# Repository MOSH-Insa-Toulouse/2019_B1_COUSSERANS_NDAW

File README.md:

# MOSH Project : LoRa Arduino Board (Martin Cousserans/Aly Ndaw)

In this project we decided to focus on the PCB design and for the programming part we just implemented the RX/TX communication in LoRa. 
For the PCB we did a board that can act like a shield or a standalone connected gas sensor in LoRa by using selectors. 

## Getting Started

In our repertory you can find the files related to the PCB in ./LoRa_Arduino_Board. In it you have the two main files :
- the schematic file : LoRa_Arduino_Board.sch 
- the pcb file : LoRa_Arduino_Board.kicad_pcb
We let all libraries in the folder so it is easy to take the project and change it. 

### kiCAD Board

The board is a 2 layers board with a ground plane on each face of the board. There are components only on the top but we have tracks on both side. 
We have in total 37 components on the board. 
We can divided the board in four parts : 
- The gas sensor and its amplification chain 
- The RN2483 module 
- The Arduino Shield connectors 
- The standalone MCU (ATMEGA 328PU)

#### The gas sensor : 
Our solution is based on connectors and jumpers to select the behavior of the board. 
JRST-2 and JRST-4 are jumpers that allow to choose a specific configuration of the gas sensor GasLeft or GasRight. JRST-3 is the select for Gas sensor 1 or Gas sensor 2. 
JRST-5 allow us to select VIN to supply the heater resistor or an external DC source. 
JRST-6 is the jumper that select the output after the amplification we can connect it to the standalone MCU or the Arduino shield. 

#### The RN2483 module : 
We use 5 pins on the RN2483 (RST, RX, TX, 3V3, GND) module and we designed 5 jumpers (JRST-1, JRX1, JTX1, JTX2, JTX3) to switch them between the arduino shield and the standalone MCU. 
We also have a voltage divider bridge to have 3v3 from the 5V of the standalone MCU to supply the RN2483. 

#### The standalone MCU : 
For the ATMEGA MCU we have designed a 5 pins connector to program the chip with the Sparkfun Interface. And also we add another jumper to choose the main supply of the board. 
You can find images of the schematic and pcb in the LoRa_Arduino_Board folder if you want to have a preview. 

### LoRa Arduino Code

For the code we decided to follow the green track to be more focused on the PCB. 
We manage to do a downlink and uplink code with the LoRa platform of https://thethingsnetwork.org

Example : loop of the downlink code 
```
void loop()
{
    led_on();

    Serial.print("TXing");
    myLora.txCnf("!"); //one byte, blocking function

    switch(myLora.txCnf("!")) //one byte, blocking function
    {
      case TX_FAIL:
      {
        Serial.println("TX unsuccessful or not acknowledged");
        break;
      }
      case TX_SUCCESS:
      {
        Serial.println("TX successful and acknowledged");
        break;
      }
      case TX_WITH_RX:
      {
        String received = myLora.getRx();
        received = myLora.base16decode(received);
        Serial.print("Received downlink: " + received);
        break;
      }
      default:
      {
        Serial.println("Unknown response from TX function");
      }
    }

    led_off();
    delay(10000);
}
```
Source codes are available in our repository in the LoRa_Arduino_Codes folder. 

## Conclusion 
If we has time we would have develop a NodeRed to do a web-service based on the Gas Sensor data.

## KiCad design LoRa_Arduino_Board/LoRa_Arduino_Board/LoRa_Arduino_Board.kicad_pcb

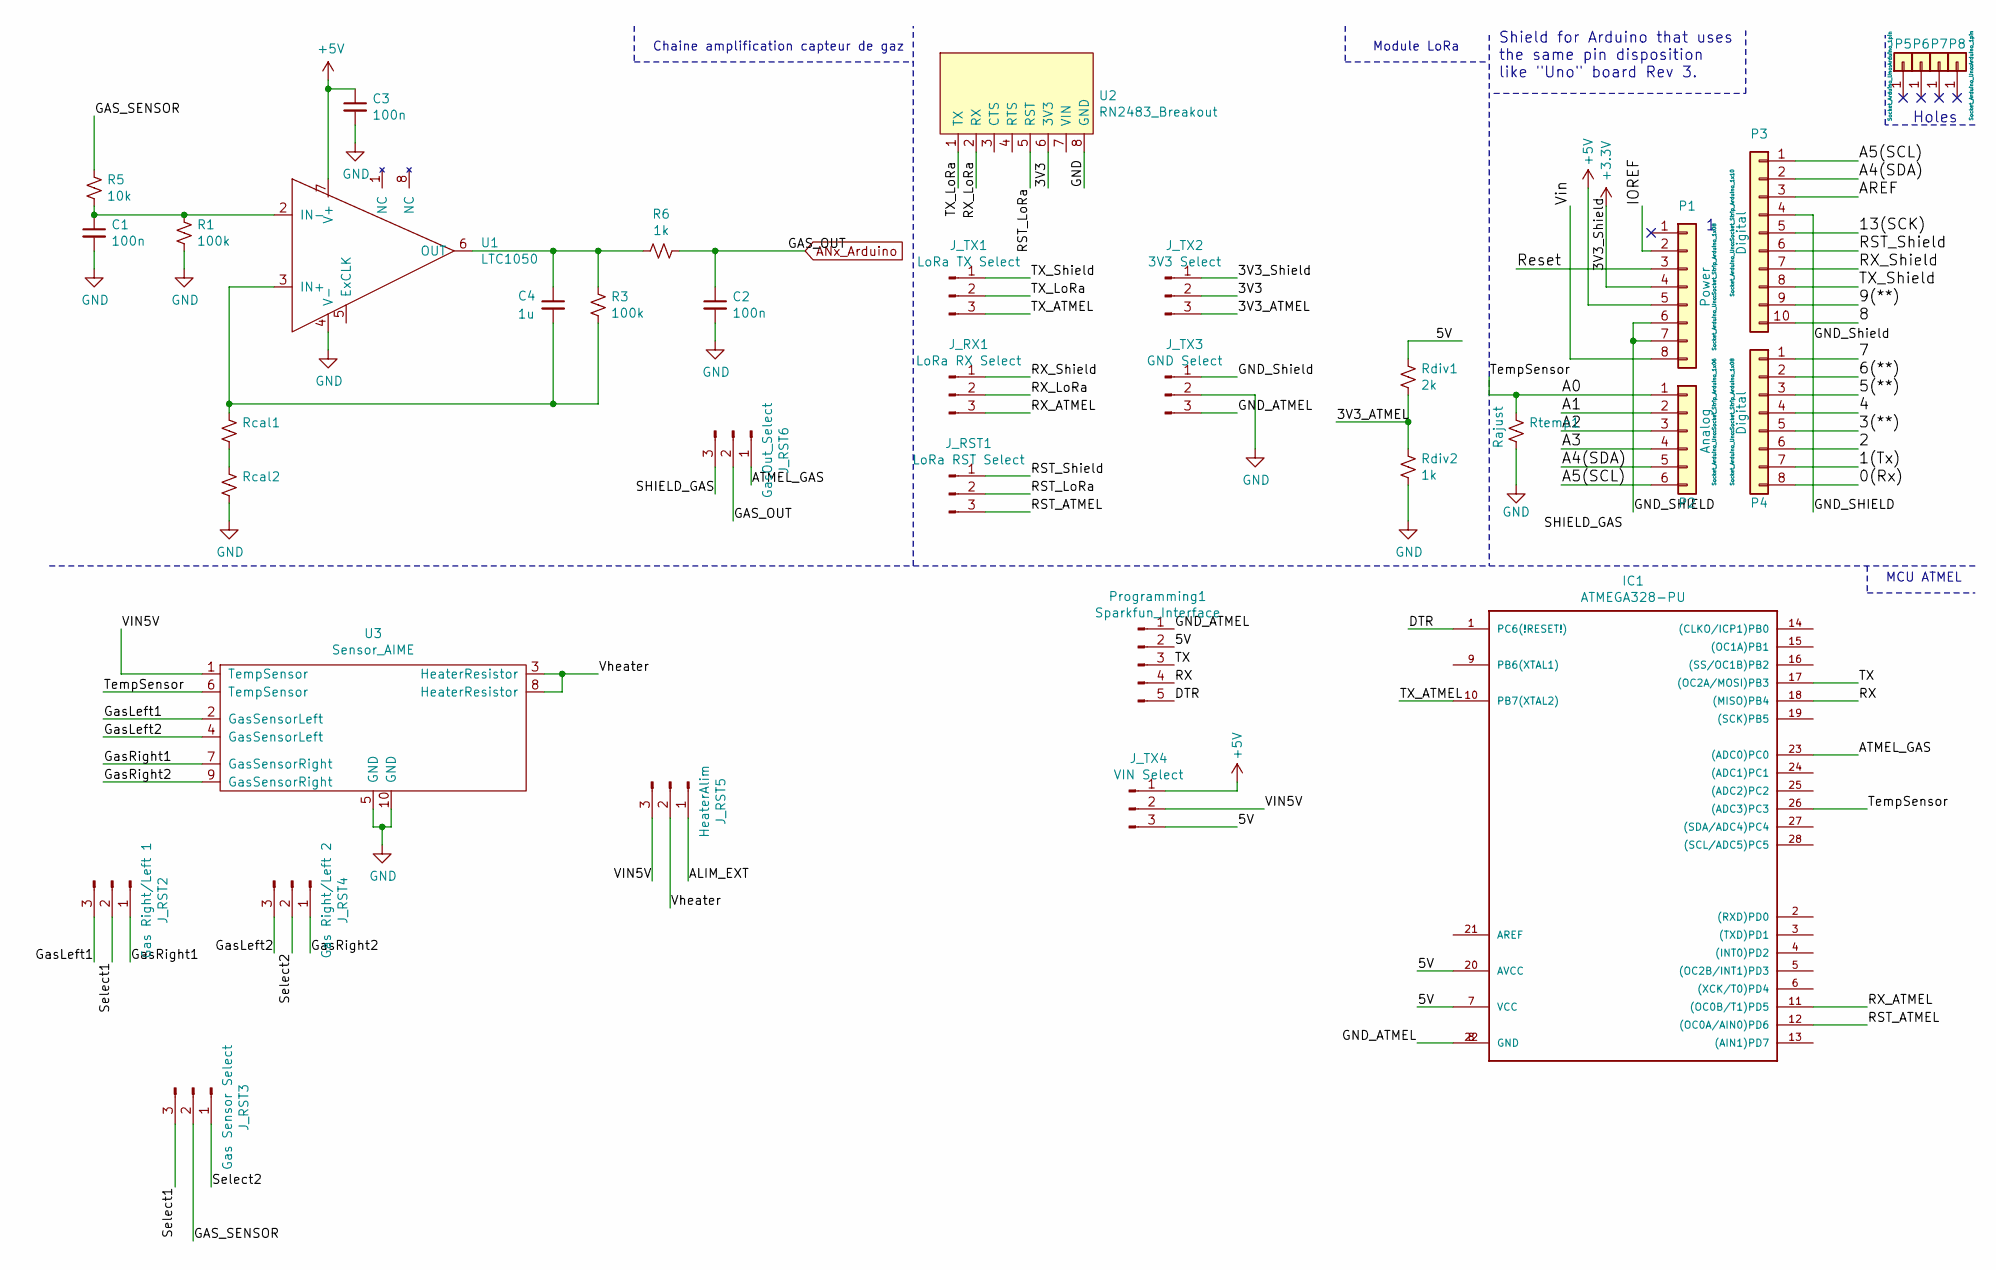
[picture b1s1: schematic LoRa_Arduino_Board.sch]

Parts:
C1, C2, C3: 100n; C_0603_1608Metric
C4: 1u; C_0603_1608Metric
IC1: ATMEGA328-PU; DIL28
J_RST1: LoRa RST Select; Molex_SL_171971-0003_1x03_P2.54mm_Vertical
J_RST2: Gas Right/Left 1; Molex_SL_171971-0003_1x03_P2.54mm_Vertical
J_RST3: Gas Sensor Select; Molex_SL_171971-0003_1x03_P2.54mm_Vertical
J_RST4: Gas Right/Left 2; Molex_SL_171971-0003_1x03_P2.54mm_Vertical
J_RST5: HeaterAlim; Molex_SL_171971-0003_1x03_P2.54mm_Vertical
J_RST6: GasOut_Select; Molex_SL_171971-0003_1x03_P2.54mm_Vertical
J_RX1: LoRa RX Select; Molex_SL_171971-0003_1x03_P2.54mm_Vertical
J_TX1: LoRa TX Select; Molex_SL_171971-0003_1x03_P2.54mm_Vertical
J_TX2: 3V3 Select; Molex_SL_171971-0003_1x03_P2.54mm_Vertical
J_TX3: GND Select; Molex_SL_171971-0003_1x03_P2.54mm_Vertical
J_TX4: VIN Select; Molex_SL_171971-0003_1x03_P2.54mm_Vertical
P1: Power; Socket_Strip_Arduino_1x08
P2: Analog; Socket_Strip_Arduino_1x06
P3: Digital; Socket_Strip_Arduino_1x10
P4: Digital; Socket_Strip_Arduino_1x08
P5, P6, P7, P8: CONN_01X01; Arduino_1pin
Programming1: Sparkfun_Interface; Molex_KK-254_AE-6410-05A_1x05_P2.54mm_Vertical
R1, R3: 100k; R_0603_1608Metric
R5: 10k; R_0603_1608Metric
R6: 1k; R_0603_1608Metric
Rcal1, Rcal2: R_0603_1608Metric
Rdiv1: 2k; R_0603_1608Metric
Rdiv2: 1k; R_0603_1608Metric
Rtemp1: Rajust; R_0603_1608Metric
U1: LTC1050; DIP-8_W7.62mm_Socket_LongPads
U2: RN2483_Breakout
U3: Sensor_AIME; TO-5-10_Window

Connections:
+3V3: P1.4
+5V: C3.1, J_TX4.1, P1.5, U1.7 (V+)
/0(Rx): P4.8
/1(Tx): P4.7
/2: P4.6
/3(**): P4.5
/3V3: J_TX2.2, U2.6 (3V3)
/3V3_ATMEL: J_TX2.3, Rdiv1.2, Rdiv2.1
/3V3_Shield: J_TX2.1
/4: P4.4
/5(**): P4.3
/5V: IC1.7 (VCC), IC1.20 (AVCC), J_TX4.3, Programming1.2, Rdiv1.1
/6(**): P4.2
/7: P4.1
/8: P3.10
/9(**): P3.9
/13(SCK): P3.5
/A0: IC1.26 ((ADC3)PC3), P2.1, Rtemp1.1, U3.6 (TempSensor)
/A1: P2.2
/A2: P2.3
/A3: P2.4
/A4(SDA): P2.5, P3.2
/A5(SCL): P2.6, P3.1
/ALIM_EXT: J_RST5.1
/AREF: P3.3
/ATMEL_GAS: IC1.23 ((ADC0)PC0), J_RST6.1
/DTR: IC1.1 (PC6(!RESET!)), Programming1.5
/GAS_SENSOR: J_RST3.2, R5.1
/GND_ATMEL: IC1.8 (GND), IC1.22 (GND), J_TX3.3, Programming1.1
/GND_SHIELD: J_TX3.1, P1.6, P1.7, P3.4
/GasLeft1: J_RST2.3, U3.2 (GasSensorLeft)
/GasLeft2: J_RST4.3, U3.4 (GasSensorLeft)
/GasRight1: J_RST2.1, U3.7 (GasSensorRight)
/GasRight2: J_RST4.1, U3.9 (GasSensorRight)
/IOREF: P1.2
/RST_ATMEL: IC1.12 ((OC0A/AIN0)PD6), J_RST1.3
/RST_LoRa: J_RST1.2, U2.5 (RST)
/RST_Shield: J_RST1.1, P3.6
/RX: IC1.18 ((MISO)PB4), Programming1.4
/RX_ATMEL: IC1.11 ((OC0B/T1)PD5), J_RX1.3
/RX_LoRa: J_RX1.2, U2.2 (RX)
/RX_Shield: J_RX1.1, P3.7
/Reset: P1.3
/SHIELD_GAS: J_RST6.3
/Select1: J_RST2.2, J_RST3.3
/Select2: J_RST3.1, J_RST4.2
/TX: IC1.17 ((OC2A/MOSI)PB3), Programming1.3
/TX_ATMEL: IC1.10 (PB7(XTAL2)), J_TX1.3
/TX_LoRa: J_TX1.2, U2.1 (TX)
/TX_Shield: J_TX1.1, P3.8
/VIN5V: J_RST5.3, J_TX4.2, U3.1 (TempSensor)
/Vheater: J_RST5.2, U3.3 (HeaterResistor), U3.8 (HeaterResistor)
/Vin: P1.8
ANx_Arduino: C2.1, J_RST6.2, R6.1
GND: C1.2, C2.2, C3.2, J_TX3.2, R1.2, Rcal2.2, Rdiv2.2, Rtemp1.2, U1.4 (V-), U2.8 (GND), U3.5 (GND), U3.10 (GND)
unnamed: C1.1, R1.1, R5.2, U1.2 (IN-)
unnamed: C4.1, R3.1, R6.2, U1.6 (OUT)
unnamed: C4.2, R3.2, Rcal1.1, U1.3 (IN+)
unnamed: Rcal1.2, Rcal2.1

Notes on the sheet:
Holes
Shield for Arduino that uses the same pin disposition like "Uno" board Rev 3.
Chaine amplification capteur de gaz
Module LoRa
MCU ATMEL

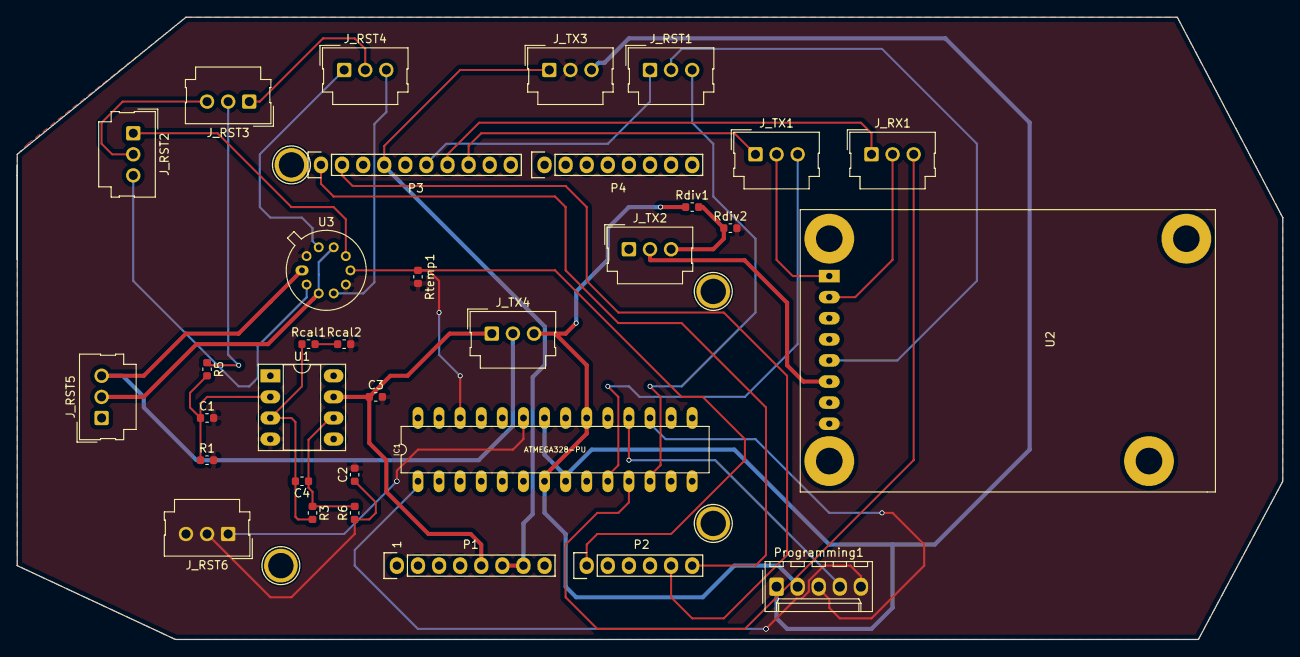
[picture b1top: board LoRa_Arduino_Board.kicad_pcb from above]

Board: 2 copper layers, 152.4 x 74.9 mm, 37 parts (0 on the bottom side), 37 nets.

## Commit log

2020-01-22 first
2020-01-22 second
2020-01-22 third
2020-01-22 images
